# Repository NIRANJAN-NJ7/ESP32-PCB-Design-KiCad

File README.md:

# ESP32-WROOM-32E Development Board — KiCad 10

Open `ESP32_DevBoard.kicad_pro` in KiCad. This revised layout is shaped as a compact development board and uses the official ESP32-WROOM-32E module footprint plus standard KiCad footprints for the headers, USB-C receptacle, regulator, passives, and buttons. The module and connector parts will appear in 3D instead of as bare custom pad outlines.

## Included

- `ESP32_DevBoard.kicad_sch`: schematic for the WROOM-32E, left/right GPIO headers, USB-C 5 V input, 5.1 kΩ CC resistors, AP2112K-3.3 regulator, decoupling capacitors, EN pull-up, and reset/boot buttons.
- `ESP32_DevBoard.kicad_pcb`: 27.94 × 58.42 mm, 2-layer board placement with 2.54 mm side headers, USB-C connector at the bottom edge, ground pours, and an antenna copper keepout.
- `ESP32_DevBoard.kicad_pro`: KiCad project settings.

## Programming and use

USB-C provides **power only** in this version. Program the ESP32 with a separate 3.3 V USB-to-UART adapter connected to GND, GPIO3/RX0, and GPIO1/TX0 on the right header. The BOOT and RESET buttons support manual bootloader entry. Do not feed 5 V into any GPIO or power the board from two 5 V sources at once.

GPIO12, GPIO0, GPIO2, GPIO5, and GPIO15 are boot strapping pins. GPIO34–GPIO39 are input-only. GPIO6–GPIO11 are reserved for the module flash and are not exposed on the headers.

## Fabrication status

This is a substantially more complete editable project, but it is still a **layout prototype**, not a board ready to order: the PCB copper tracks are not routed, and ERC/DRC plus the exact selected parts and manufacturer clearances have not been checked. Route the connections, run ERC and DRC, and inspect the Gerbers before fabrication.

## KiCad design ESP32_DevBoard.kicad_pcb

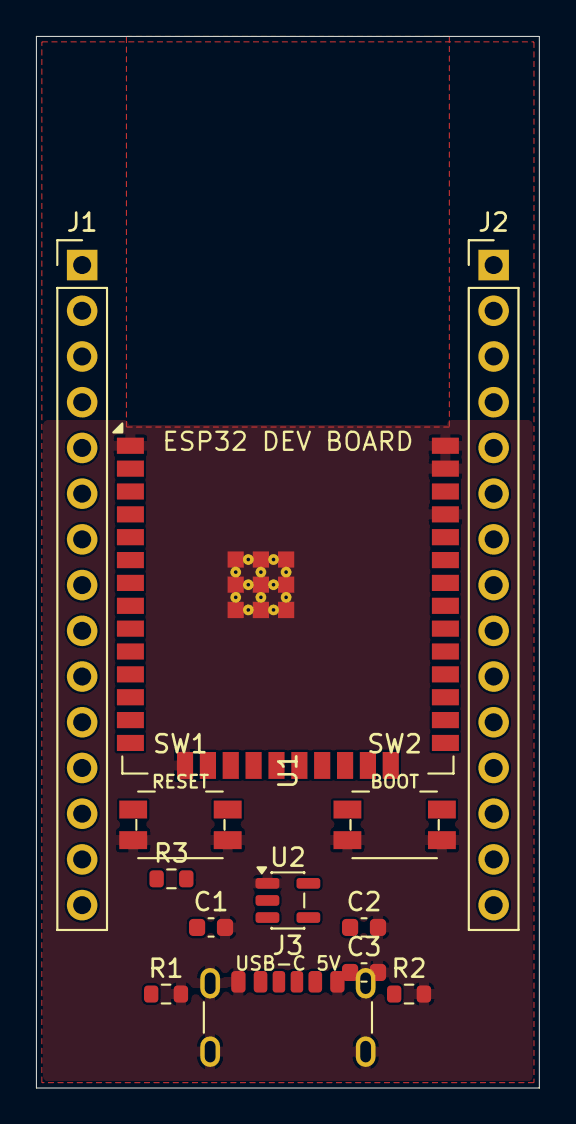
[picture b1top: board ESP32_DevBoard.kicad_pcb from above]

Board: 2 copper layers, 27.9 x 58.4 mm, 13 parts (0 on the bottom side), 28 nets, no tracks yet.

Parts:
C1, C2: 10uF; C_0603_1608Metric
C3: 100nF; C_0603_1608Metric
J1: GPIO / POWER LEFT; PinHeader_1x15_P2.54mm_Vertical
J2: GPIO / POWER RIGHT; PinHeader_1x15_P2.54mm_Vertical
J3: USB-C POWER; USB_C_Receptacle_GCT_USB4125-xx-x_6P_TopMnt_Horizontal
R1, R2: 5.1k; R_0603_1608Metric
R3: 10k; R_0603_1608Metric
SW1: RESET; Panasonic_EVQPUJ_EVQPUA
SW2: BOOT; Panasonic_EVQPUJ_EVQPUA
U1: ESP32-WROOM-32E
U2: AP2112K-3.3; SOT-23-5

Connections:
+3V3: C2.1, C3.1, J1.2, R3.1, U1.2, U1.36, U2.2
+5V: C1.1, J2.2, J3.A9, J3.B9, U2.3, U2.4
CC1: J3.A5, R1.1
CC2: J3.B5, R2.1
EN: R3.2, SW1.1, U1.3
GND: C1.2, C2.2, C3.2, J1.1, J2.1, J3.A12, J3.B12, J3.SH, R1.2, R2.2, SW1.2, SW2.2, U1.1, U1.15, U1.35, U1.37, U1.38, U1.39, U2.1
GPIO0: J2.13, SW2.1, U1.25
GPIO1: J2.14, U1.34
GPIO3: J2.15, U1.33
GPIO4: J2.8, U1.26
GPIO5: J2.9, U1.29
GPIO12: J2.10, U1.14
GPIO13: J1.3, U1.16
GPIO14: J1.4, U1.13
GPIO15: J2.11, U1.23
GPIO16: J1.5, U1.27
GPIO17: J1.6, U1.28
GPIO18: J1.7, U1.30
GPIO19: J1.8, U1.31
GPIO25: J1.12, U1.10
GPIO26: J1.13, U1.11
GPIO27: J1.14, U1.12
GPIO32: J1.15, U1.8
GPIO33: J2.3, U1.9
GPIO34: J2.4, U1.6
GPIO35: J2.5, U1.7
GPIO36: J2.6, U1.4
GPIO39: J2.7, U1.5
